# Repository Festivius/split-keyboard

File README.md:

# Split Keyboard

A 52-key wireless split keyboard built based on Hack Club's Blueprint event. The layout is inspired from the Voyager split keyboard.

## Features
- 2 halves made using an nRF52840 board.
- Keyboard matricies with a diode per key to prevent ghosting. 
- Firmware made using ZMK.

## Full Assembly

## CAD Files

## PCB Image

## Schematics

## Cart Screenshots

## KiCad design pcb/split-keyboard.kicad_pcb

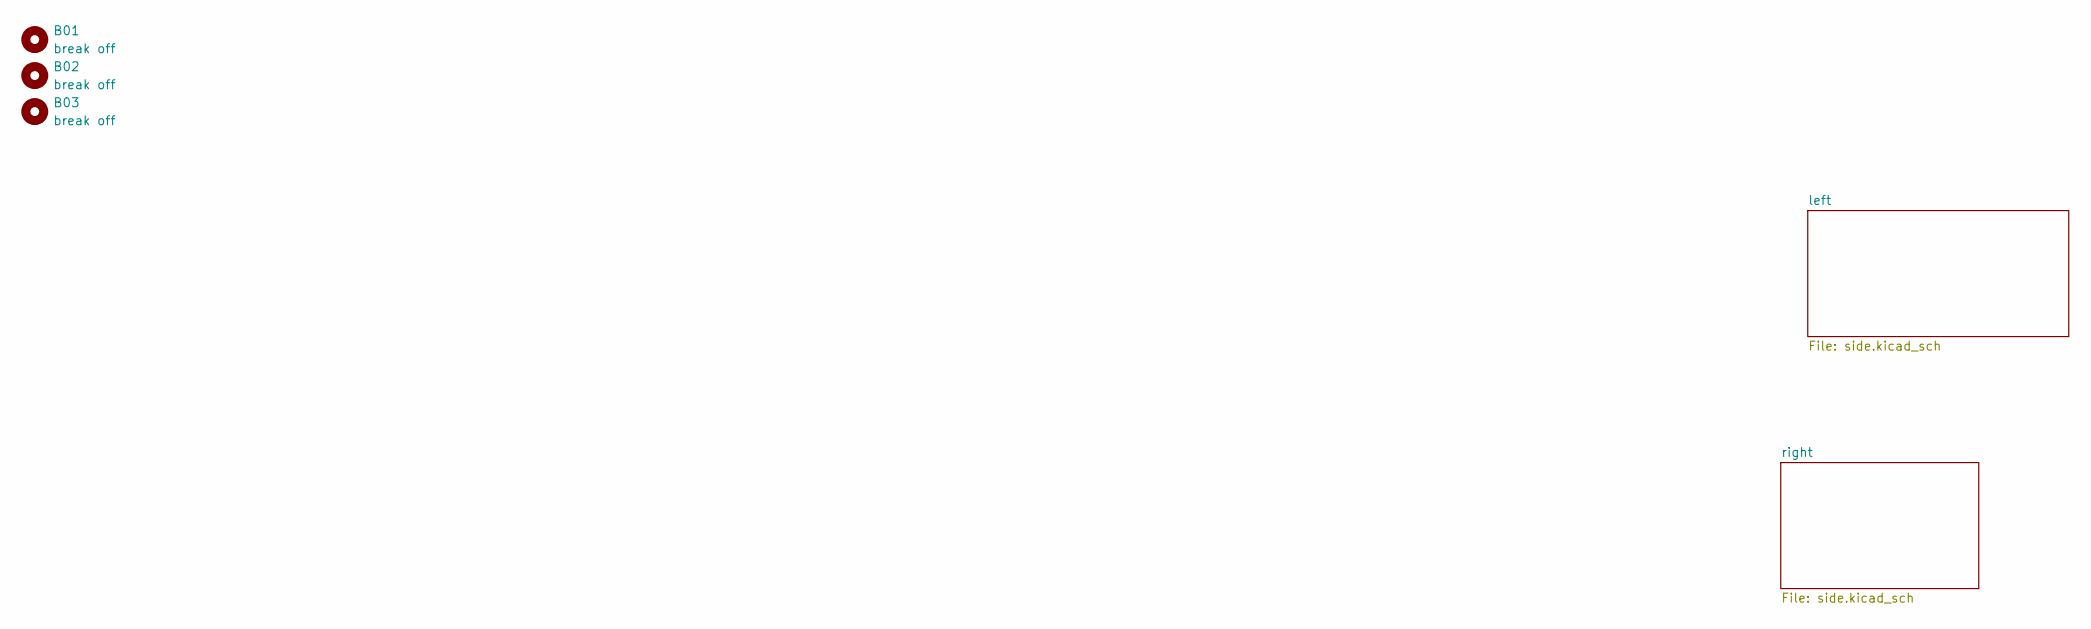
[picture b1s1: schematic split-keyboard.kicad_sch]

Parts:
B01, B02, B03: break off; mouse-bite-5mm-slot

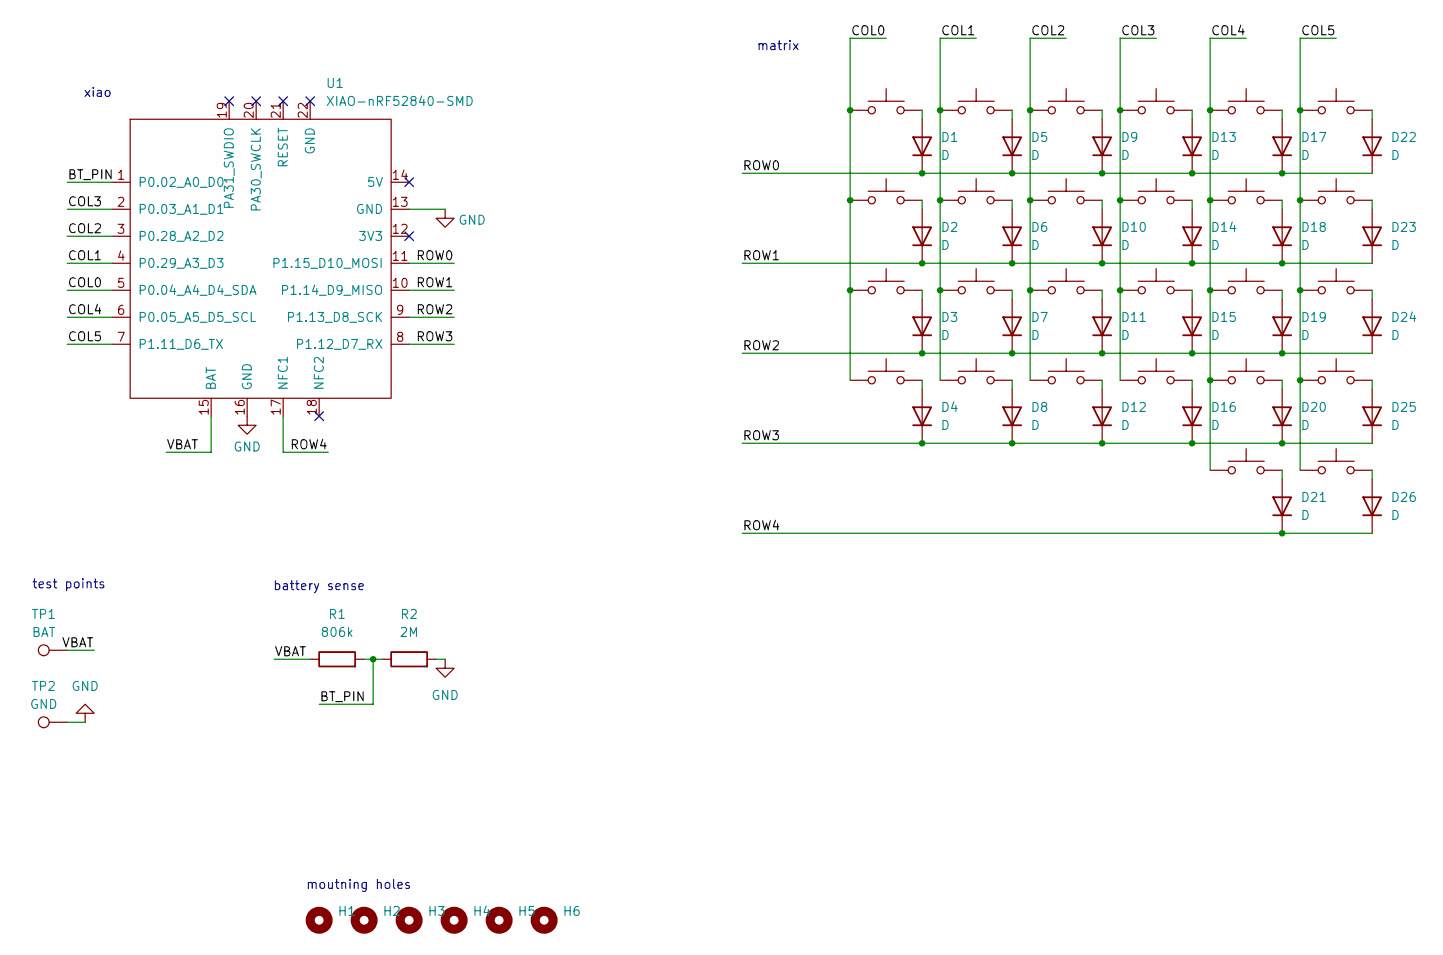
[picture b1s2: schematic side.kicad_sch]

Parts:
D1, D2, D3, D4, D5, D6, D7, D8, D9, D10, D11, D12, D13, D14, D15, D16, D17, D18, D19, D20, D21, D22, D23, D24, D25, D26: D; D_SOD-123
H1, H2, H3, H4, H5, H6: MountingHole; MountingHole_2.7mm_M2.5
R1: 806k; R_0805_2012Metric
R2: 2M; R_0805_2012Metric
SW1, SW2, SW3, SW4, SW5, SW6, SW7, SW8, SW9, SW10, SW11, SW12, SW13, SW14, SW15, SW16, SW17, SW18, SW19, SW20, SW21, SW22, SW23, SW24, SW25: SW_Push; SW_MX_HS_KS-2P02B01-01_1u
SW26: SW_Push; SW_MX_HS_KS-2P02B01-01_1.75u
TP1: BAT; TestPoint_Pad_D4.0mm
TP2: GND; TestPoint_Pad_D4.0mm
U1: XIAO-nRF52840-SMD; modified-XIAO-nRF52840-SMD

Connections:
/left/BT_PIN: R1.2, R2.1, U1.1 (P0.02_A0_D0)
/left/COL0: SW1.1, SW2.1, SW3.1, SW4.1, U1.5 (P0.04_A4_D4_SDA)
/left/COL1: SW5.1, SW6.1, SW7.1, SW8.1, U1.4 (P0.29_A3_D3)
/left/COL2: SW9.1, SW10.1, SW11.1, SW12.1, U1.3 (P0.28_A2_D2)
/left/COL3: SW13.1, SW14.1, SW15.1, SW16.1, U1.2 (P0.03_A1_D1)
/left/COL4: SW17.1, SW18.1, SW19.1, SW20.1, SW21.1, U1.6 (P0.05_A5_D5_SCL)
/left/COL5: SW22.1, SW23.1, SW24.1, SW25.1, SW26.1, U1.7 (P1.11_D6_TX)
/left/ROW0: D1.1 (K), D5.1 (K), D9.1 (K), D13.1 (K), D17.1 (K), D22.1 (K), U1.11 (P1.15_D10_MOSI)
/left/ROW1: D2.1 (K), D6.1 (K), D10.1 (K), D14.1 (K), D18.1 (K), D23.1 (K), U1.10 (P1.14_D9_MISO)
/left/ROW2: D3.1 (K), D7.1 (K), D11.1 (K), D15.1 (K), D19.1 (K), D24.1 (K), U1.9 (P1.13_D8_SCK)
/left/ROW3: D4.1 (K), D8.1 (K), D12.1 (K), D16.1 (K), D20.1 (K), D25.1 (K), U1.8 (P1.12_D7_RX)
/left/ROW4: D21.1 (K), D26.1 (K), U1.17 (NFC1)
/left/VBAT: R1.1, TP1.1, U1.15 (BAT)
GND: R2.2, TP2.1, U1.13 (GND), U1.16 (GND); also elsewhere on the board
unnamed: D1.2 (A), SW1.2
unnamed: D2.2 (A), SW2.2
unnamed: D3.2 (A), SW3.2
unnamed: D4.2 (A), SW4.2
unnamed: D5.2 (A), SW5.2
unnamed: D6.2 (A), SW6.2
unnamed: D7.2 (A), SW7.2
unnamed: D8.2 (A), SW8.2
unnamed: D9.2 (A), SW9.2
unnamed: D10.2 (A), SW10.2
unnamed: D11.2 (A), SW11.2
unnamed: D12.2 (A), SW12.2
unnamed: D13.2 (A), SW13.2
unnamed: D14.2 (A), SW14.2
unnamed: D15.2 (A), SW15.2
unnamed: D16.2 (A), SW16.2
unnamed: D17.2 (A), SW17.2
unnamed: D18.2 (A), SW18.2
unnamed: D19.2 (A), SW19.2
unnamed: D20.2 (A), SW20.2
unnamed: D21.2 (A), SW21.2
unnamed: D22.2 (A), SW22.2
unnamed: D23.2 (A), SW23.2
unnamed: D24.2 (A), SW24.2
unnamed: D25.2 (A), SW25.2
unnamed: D26.2 (A), SW26.2

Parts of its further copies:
D27, D28, D29, D30, D31, D32, D33, D34, D35, D36, D37, D38, D39, D40, D41, D42, D43, D44, D45, D46, D47, D48, D49, D50, D51, D52: D; D_SOD-123
H7, H8, H9, H10, H11, H12: MountingHole; MountingHole_2.7mm_M2.5
R3: 806k; R_0805_2012Metric
R4: 2M; R_0805_2012Metric
SW27, SW28, SW29, SW30, SW31, SW32, SW33, SW34, SW35, SW36, SW37, SW38, SW39, SW40, SW41, SW42, SW43, SW44, SW45, SW46, SW47, SW48, SW49, SW50, SW51: SW_Push; SW_MX_HS_KS-2P02B01-01_1u
SW52: SW_Push; SW_MX_HS_KS-2P02B01-01_1.75u
TP3: BAT; TestPoint_Pad_D4.0mm
TP4: GND; TestPoint_Pad_D4.0mm
U2: XIAO-nRF52840-SMD; modified-XIAO-nRF52840-SMD

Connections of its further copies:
/right/BT_PIN: R3.2, R4.1, U2.1 (P0.02_A0_D0)
/right/COL0: SW27.1, SW28.1, SW29.1, SW30.1, U2.5 (P0.04_A4_D4_SDA)
/right/COL1: SW31.1, SW32.1, SW33.1, SW34.1, U2.4 (P0.29_A3_D3)
/right/COL2: SW35.1, SW36.1, SW37.1, SW38.1, U2.3 (P0.28_A2_D2)
/right/COL3: SW39.1, SW40.1, SW41.1, SW42.1, U2.2 (P0.03_A1_D1)
/right/COL4: SW43.1, SW44.1, SW45.1, SW46.1, SW47.1, U2.6 (P0.05_A5_D5_SCL)
/right/COL5: SW48.1, SW49.1, SW50.1, SW51.1, SW52.1, U2.7 (P1.11_D6_TX)
/right/ROW0: D27.1 (K), D31.1 (K), D35.1 (K), D39.1 (K), D43.1 (K), D48.1 (K), U2.11 (P1.15_D10_MOSI)
/right/ROW1: D28.1 (K), D32.1 (K), D36.1 (K), D40.1 (K), D44.1 (K), D49.1 (K), U2.10 (P1.14_D9_MISO)
/right/ROW2: D29.1 (K), D33.1 (K), D37.1 (K), D41.1 (K), D45.1 (K), D50.1 (K), U2.9 (P1.13_D8_SCK)
/right/ROW3: D30.1 (K), D34.1 (K), D38.1 (K), D42.1 (K), D46.1 (K), D51.1 (K), U2.8 (P1.12_D7_RX)
/right/ROW4: D47.1 (K), D52.1 (K), U2.17 (NFC1)
/right/VBAT: R3.1, TP3.1, U2.15 (BAT)
GND: R4.2, TP4.1, U2.13 (GND), U2.16 (GND); also elsewhere on the board
unnamed: D27.2 (A), SW27.2
unnamed: D28.2 (A), SW28.2
unnamed: D29.2 (A), SW29.2
unnamed: D30.2 (A), SW30.2
unnamed: D31.2 (A), SW31.2
unnamed: D32.2 (A), SW32.2
unnamed: D33.2 (A), SW33.2
unnamed: D34.2 (A), SW34.2
unnamed: D35.2 (A), SW35.2
unnamed: D36.2 (A), SW36.2
unnamed: D37.2 (A), SW37.2
unnamed: D38.2 (A), SW38.2
unnamed: D39.2 (A), SW39.2
unnamed: D40.2 (A), SW40.2
unnamed: D41.2 (A), SW41.2
unnamed: D42.2 (A), SW42.2
unnamed: D43.2 (A), SW43.2
unnamed: D44.2 (A), SW44.2
unnamed: D45.2 (A), SW45.2
unnamed: D46.2 (A), SW46.2
unnamed: D47.2 (A), SW47.2
unnamed: D48.2 (A), SW48.2
unnamed: D49.2 (A), SW49.2
unnamed: D50.2 (A), SW50.2
unnamed: D51.2 (A), SW51.2
unnamed: D52.2 (A), SW52.2

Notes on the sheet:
battery sense
test points
moutning holes
xiao
matrix

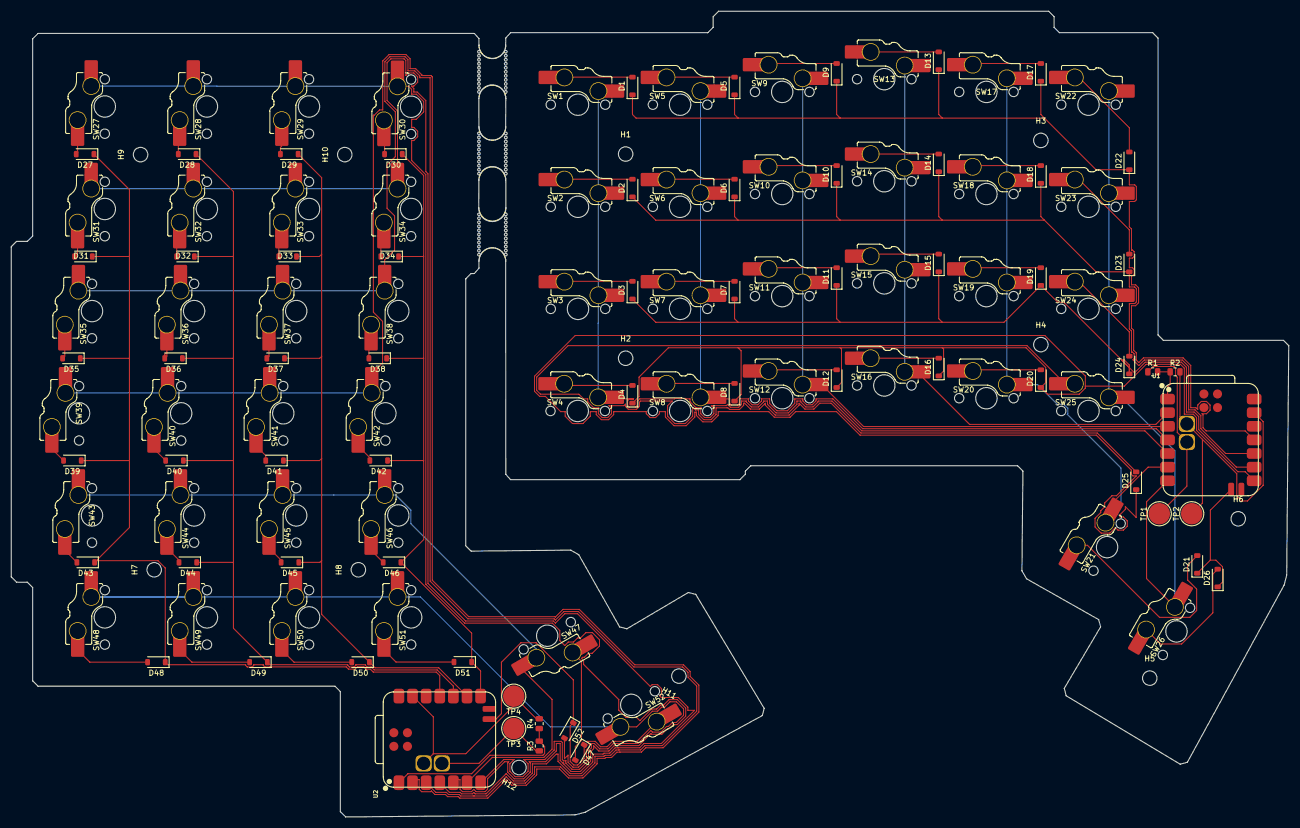
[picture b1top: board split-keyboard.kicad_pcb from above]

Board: 2 copper layers, 238.4 x 150.3 mm, 129 parts (0 on the bottom side), 79 nets.

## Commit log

2026-01-02 added pcb
2026-01-02 moved pcb to folder
2026-01-18 Rename split-keyboard-case-bottom.stl to case/split-keyboard-case-bottom.stl
2026-01-18 Rename split-keyboard-case-top.stl to case/split-keyboard-case-top.stl
2026-01-22 Add firmware as submodule
2026-01-22 Remove broken zmk submodule entry
2026-01-22 Add ZMK firmware as submodule
2026-01-22 Ignore macOS .DS_Store
2026-01-22 Remove .DS_Store
2026-01-22 Add link to Google Sheets document in README
2026-01-23 Add project details for split keyboard
    Added detailed information about the split keyboard project, including assembly, CAD files, PCB image, schematics, and BOM link.
2026-01-23 Revise README for clarity and feature listing
    Updated the README to clarify the keyboard's features and origin.
2026-03-29 Rename split-keyboard-case-bottom.step to case/split-keyboard-case-bottom.step
2026-03-29 Rename split-keyboard-case-top.step to case/split-keyboard-case-top.step
2026-03-29 Replace BOM Google Spreadsheet section with Cart Screenshots
